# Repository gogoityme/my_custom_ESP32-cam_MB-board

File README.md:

# my_custom_ESP32-cam_MB-board
This is my hackclub-forge project that I built in KiCad software. It was fun sidequest (I wanted to build something else and found out that my programer is broken so I made this instead). It was quite challenging for me because this was my first ever schematic and pcb design (because of that the scematic is very messy). But I had so much fun learning something new.
# I dont know how to upload and order something from pcb-way so it has not been tried yet

# here are some pictures

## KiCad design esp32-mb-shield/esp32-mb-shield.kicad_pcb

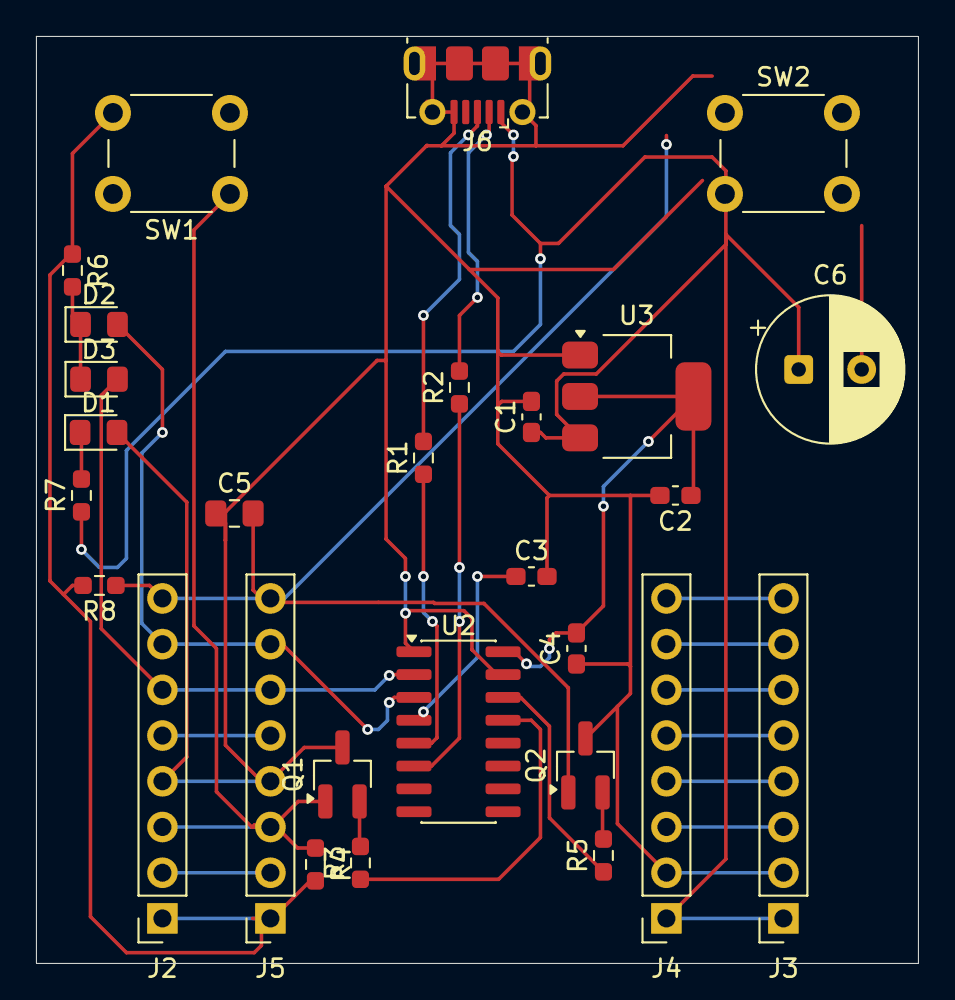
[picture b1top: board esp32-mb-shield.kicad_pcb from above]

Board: 2 copper layers, 49.0 x 51.5 mm, 28 parts (0 on the bottom side), 26 nets.

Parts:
C1, C2, C3, C4: 100µF; C_0603_1608Metric_Pad1.08x0.95mm_HandSolder
C5: 1µF; C_0805_2012Metric_Pad1.18x1.45mm_HandSolder
C6: 470µF; CP_Radial_D8.0mm_P3.50mm
D1, D2, D3: LED; LED_0805_2012Metric_Pad1.15x1.40mm_HandSolder
J2, J3, J4, J5: Conn_01x08_Socket; PinSocket_1x08_P2.54mm_Vertical
J6: USB_B_Micro; USB_Micro-B_Molex-105017-0001
Q1, Q2: NPN; SOT-23_Handsoldering
R1, R2: 22; R_0603_1608Metric_Pad0.98x0.95mm_HandSolder
R3, R4, R5, R8: 10k; R_0603_1608Metric_Pad0.98x0.95mm_HandSolder
R6, R7: 1k; R_0603_1608Metric_Pad0.98x0.95mm_HandSolder
SW1, SW2: SW_Push; SW_PUSH_6mm
U2: CH340C; SOIC-16_3.9x9.9mm_P1.27mm
U3: AMS1117-3.3; SOT-223-3_TabPin2

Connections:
unnamed: C1.2, C2.2, C3.2, C4.1, C5.1, C6.2, D1.2 (A), J2.4, J3.2, J4.2, J5.4, J6.5 (GND), J6.SH (Shield), Q1.3 (E), Q2.3 (E), SW2.2, U2.1 (GND), U2.15 (R232), U3.1 (GND)
unnamed: D1.1 (K), R7.2
unnamed: D2.2 (A), J2.7, J5.7, U2.3 (RXD)
unnamed: D2.1 (K), D3.1 (K), R6.2
unnamed: D3.2 (A), J2.6, J5.6, U2.2 (TXD)
unnamed: J2.1, J5.1, R4.2, R6.1, R8.2, SW1.2
unnamed: J2.2, J5.2
unnamed: J2.3, J5.3, Q1.1 (C), R4.1, SW1.1
unnamed: J2.5, J5.5
unnamed: C5.2, J2.8, J5.8, Q2.1 (C), R8.1, SW2.1
unnamed: C1.1, C6.1, J3.1, J4.1, J6.1 (VBUS), R7.1, U3.3 (VI)
unnamed: J3.3, J4.3
unnamed: J3.4, J4.4
unnamed: J3.5, J4.5
unnamed: J3.6, J4.6
unnamed: J3.7, J4.7
unnamed: J3.8, J4.8
unnamed: J6.3 (D+), R1.2
unnamed: J6.2 (D-), R2.2
unnamed: Q1.2 (B), R3.2
unnamed: Q2.2 (B), R5.2
unnamed: R1.1, U2.5 (UD+)
unnamed: R2.1, U2.6 (UD-)
unnamed: C2.1, C3.1, C4.2, U2.4 (V3), U2.16 (VCC), U3.2 (VO)
unnamed: R3.1, U2.13 (~DTR)
unnamed: R5.1, U2.14 (~RTS)
